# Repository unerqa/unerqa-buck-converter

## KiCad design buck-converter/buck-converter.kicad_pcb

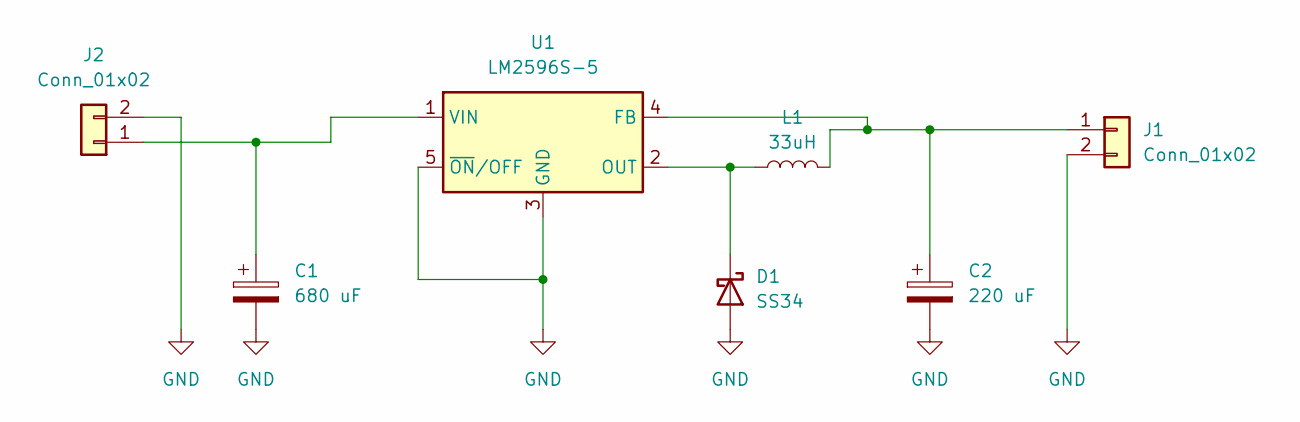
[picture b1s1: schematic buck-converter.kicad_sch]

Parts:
C1: 680 uF; CP_Elec_10x10
C2: 220 uF; CP_Elec_8x10.5
D1: SS34; D_SMC
J1, J2: Conn_01x02; TerminalBlock_Phoenix_MKDS-1,5-2-5.08_1x02_P5.08mm_Horizont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
L1: 33uH; L_12x12mm_H8mm
U1: LM2596S-5; TO-263-5_TabPin3

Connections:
GND: C1.2, C2.2, D1.2 (A), J1.2, J2.2, U1.3 (GND), U1.5 (~ON/OFF)
unnamed: D1.1 (K), L1.1, U1.2 (OUT)
unnamed: C2.1, J1.1, L1.2, U1.4 (FB)
unnamed: C1.1, J2.1, U1.1 (VIN)

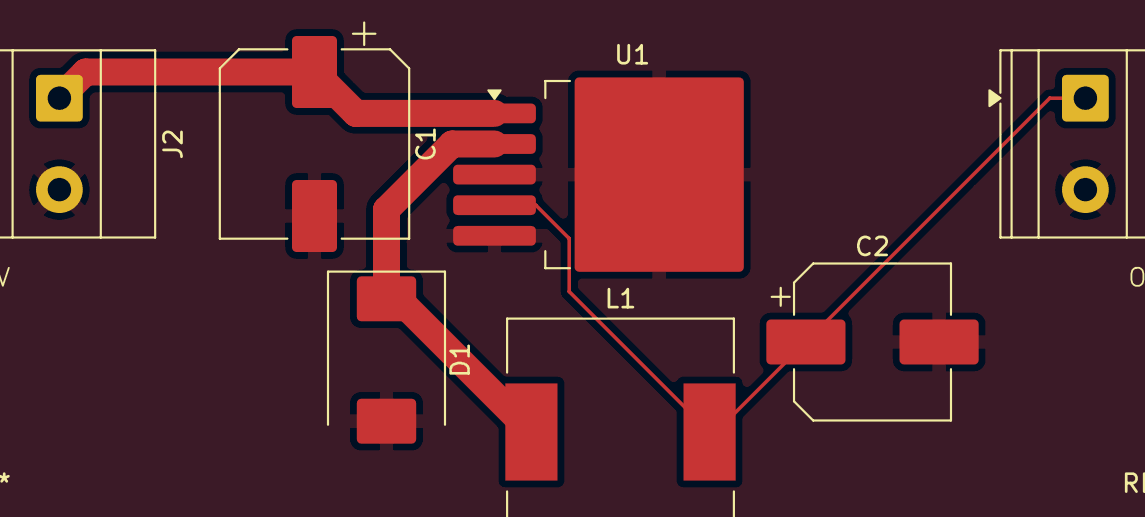
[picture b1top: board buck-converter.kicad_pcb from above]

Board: 2 copper layers, 7 parts (0 on the bottom side), 4 nets.
